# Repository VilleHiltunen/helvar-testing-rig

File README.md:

# helvar-testing-rig

This repository is for holding software and other project artifacts from the Aalto-University protopaja 2019 course
from project group 4. Everything here is under the Creative Commons Attribution 4.0 International License, with two 
exceptions: The KiCAD Arduino board symbols and footprints which are licensed under LGPL under the name of 
Nicholas Parks Young at https://github.com/Alarm-Siren/arduino-kicad-library. The original readme can be found in 
the MegaShield folder.

The second exception is the software code, which is written under the MIT license, and is totally free for grabs.

NOTE: There is a current (01.09.2019) bug in the Windows Arduino AVR compiler, so the Arduino mega code might not compile
with the latest board definitions. This can be fixed by downgrading the board definitions from the boards manager. See:
https://arduino.stackexchange.com/questions/58495/strange-compiler-error-segmentation-fault

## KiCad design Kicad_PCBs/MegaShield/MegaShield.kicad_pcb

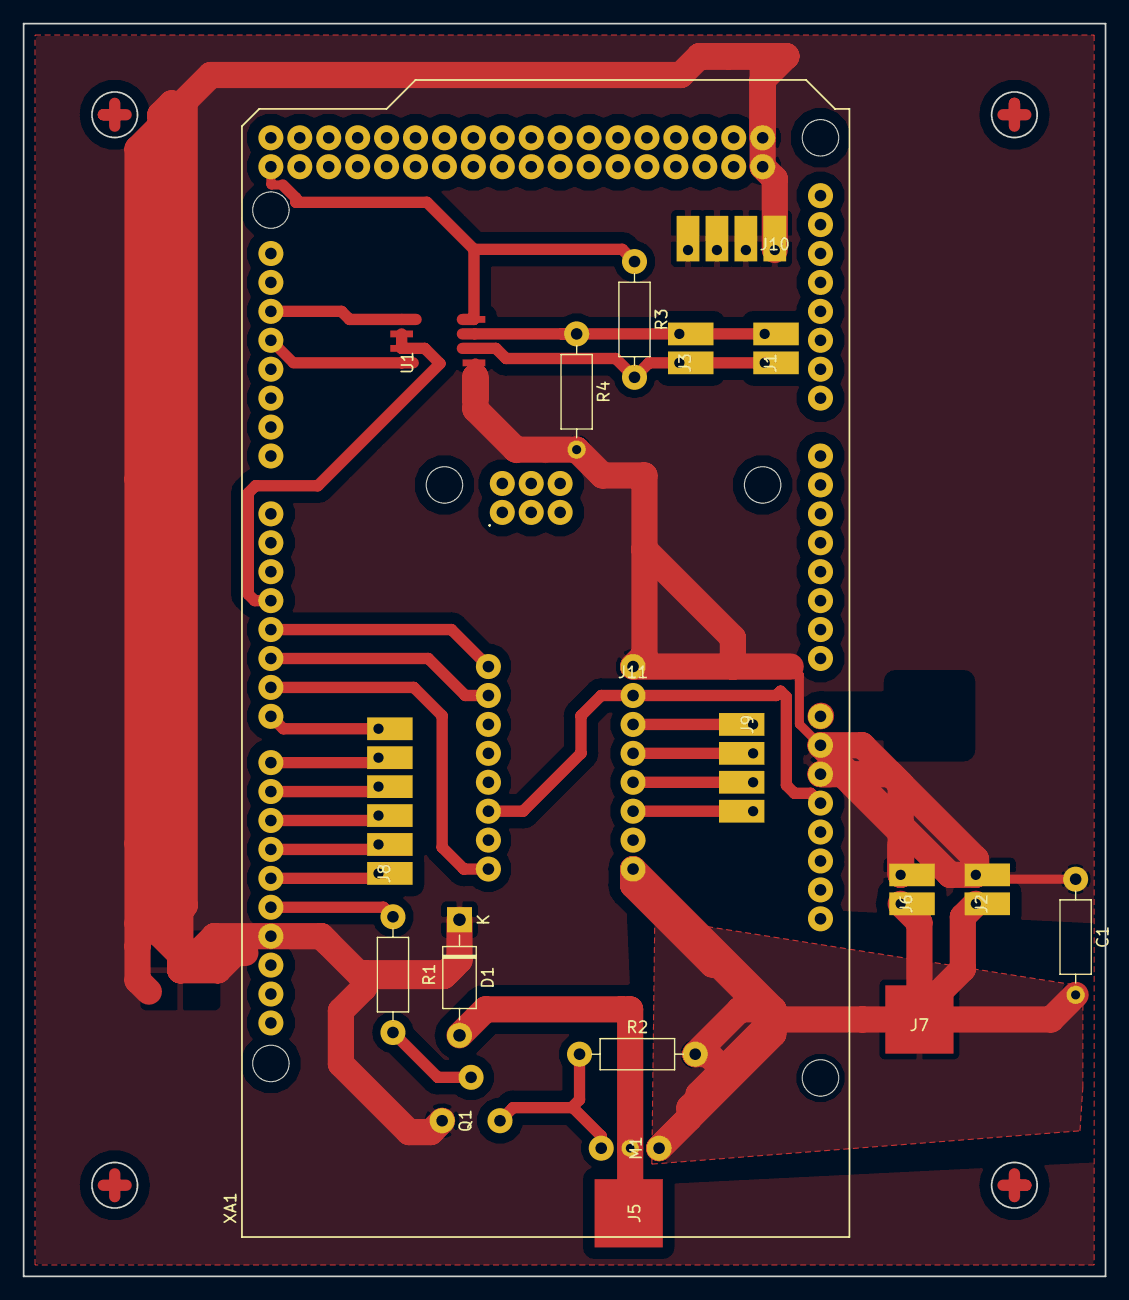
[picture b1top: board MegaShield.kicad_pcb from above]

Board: 2 copper layers, 95.0 x 110.0 mm, 20 parts (0 on the bottom side), 25 nets.

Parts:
C1: 47u; R_Axial_DIN0207_L6.3mm_D2.5mm_P10.16mm_Horizontal
D1: DIODE; D_DO-41_SOD81_P10.16mm_Horizontal
J1, J3: rs485conn; 2_2.54
J2: Ypow; 2_2.54
J5: HeatingOut; VinPad
J6: Xpow; 2_2.54
J7: 12V_VIN; VinPad
J8: SensorLimits; 6_2.54
J9: SenStepper; 4_2.54
J10: limitSwitches; 4_2.54
J11: tmc2208; StepStick
M1: FQP27P06; MOSFET
Q1: 2N3904; BJT
R1: 10k; R_Axial_DIN0207_L6.3mm_D2.5mm_P10.16mm_Horizontal
R2: 1k; R_Axial_DIN0207_L6.3mm_D2.5mm_P10.16mm_Horizontal
R3, R4: R; R_Axial_DIN0207_L6.3mm_D2.5mm_P10.16mm_Horizontal
U1: MAX1487E; NSOIC-8
XA1: Arduino_Mega2560_Shield

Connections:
5V: J11.2, J11.14, R3.1, U1.8, XA1.5V1, XA1.5V3, XA1.5V4
12V: C1.2, J2.1, J6.1, J7.1, J11.8, M1.3, R2.2
DIR: J11.9, XA1.D4
DR: U1.2, U1.3, XA1.D3
EN: J11.16, XA1.D6
GND: C1.1, D1.1, J2.2, J6.2, J10.1, J10.2, J10.3, J10.4, J11.1, Q1.1, R4.2, U1.5, XA1.GND1, XA1.GND2, XA1.GND3, XA1.GND5, XA1.GND6
HEAT: R1.1, XA1.D13
unnamed: D1.2, J5.1, M1.1
unnamed: J1.1, J3.1, R3.2, U1.6
unnamed: J1.2, J3.2, R4.1, U1.7
unnamed: J9.1, J11.3
unnamed: J9.2, J11.4
unnamed: J9.3, J11.5
unnamed: J9.4, J11.6
unnamed: M1.2, Q1.3, R2.1
unnamed: Q1.2, R1.2
unnamed: U1.1, XA1.D18
unnamed: U1.4, XA1.D19
SEN_LL: J8.5, XA1.D8
SEN_RL: J8.6, XA1.D7
STEP: J11.10, XA1.D5
X_LL: J8.3, XA1.D10
X_RL: J8.4, XA1.D9
Y_LL: J8.1, XA1.D12
Y_RL: J8.2, XA1.D11

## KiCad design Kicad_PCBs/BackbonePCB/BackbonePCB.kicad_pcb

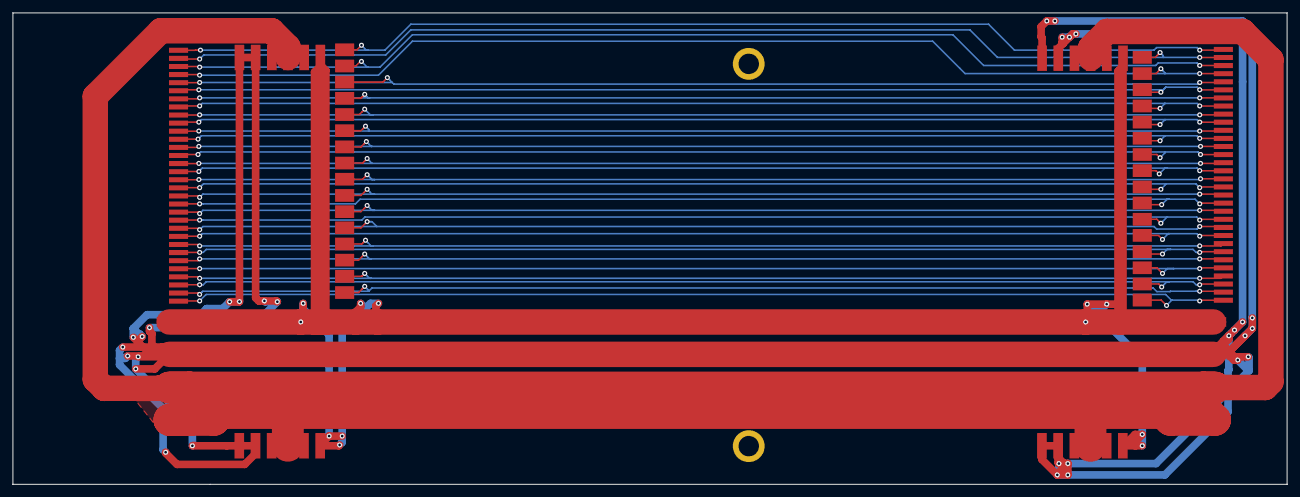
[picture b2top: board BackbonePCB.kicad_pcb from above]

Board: 2 copper layers, 200.0 x 74.0 mm, 14 parts (0 on the bottom side), 35 nets.

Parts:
H1, H2: MountingHole; Screw_Hole
J1, J2, J7, J8: Conn_01x02_Female; SMD_Connector_2X
J3, J4, J5, J6: Conn_01x06_Female; SMD_Connector_6X
J9, J12: Conn_01x32_Female; Connector_32x
J10, J11: Conn_01x16_Female; Connector_16x

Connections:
/5V: J2.2, J3.6, J4.1, J5.6, J6.1, J8.1
/12V: J2.1, J3.1, J3.2, J4.5, J4.6, J5.1, J5.2, J6.5, J6.6, J8.2
/GND: J1.1, J1.2, J3.3, J3.4, J3.5, J4.2, J4.3, J4.4, J5.3, J5.4, J5.5, J6.2, J6.3, J6.4, J7.1, J7.2
unnamed: J9.32, J10.1, J12.1
unnamed: J9.30, J10.2, J12.3
unnamed: J9.28, J10.3, J12.5
unnamed: J9.26, J10.4, J12.7
unnamed: J9.24, J10.5, J12.9
unnamed: J9.22, J10.6, J12.11
unnamed: J9.20, J10.7, J12.13
unnamed: J9.18, J10.8, J12.15
unnamed: J9.16, J10.9, J12.17
unnamed: J9.14, J10.10, J12.19
unnamed: J9.12, J10.11, J12.21
unnamed: J9.10, J10.12, J12.23
unnamed: J9.8, J10.13, J12.25
unnamed: J9.6, J10.14, J12.27
unnamed: J9.4, J10.15, J12.29
unnamed: J9.2, J10.16, J12.31
unnamed: J9.1, J11.1, J12.32
unnamed: J9.3, J11.2, J12.30
unnamed: J9.5, J11.3, J12.28
unnamed: J9.7, J11.4, J12.26
unnamed: J9.9, J11.5, J12.24
unnamed: J9.11, J11.6, J12.22
unnamed: J9.13, J11.7, J12.20
unnamed: J9.15, J11.8, J12.18
unnamed: J9.17, J11.9, J12.16
unnamed: J9.19, J11.10, J12.14
unnamed: J9.21, J11.11, J12.12
unnamed: J9.23, J11.12, J12.10
unnamed: J9.25, J11.13, J12.8
unnamed: J9.27, J11.14, J12.6
unnamed: J9.29, J11.15, J12.4
unnamed: J9.31, J11.16, J12.2

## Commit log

2019-09-01 Added project files
2019-09-01 Added readme of sorts
2019-09-01 Made sure licenses line up
2019-09-01 Updated bunch of stuff
2019-09-01 Fixed savefile
2019-09-02 Added start guide and parts list, commented code
2019-09-02 Added a bunch of resources
2019-09-02 Trying to change MIT license into CC
2019-09-02 Added the new license
2019-09-02 It's actually called a license
2019-09-02 Fixed readme to reflex license
